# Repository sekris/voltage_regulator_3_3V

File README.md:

# voltage_regulator_3_3V
5v to 3.3v voltage regulator

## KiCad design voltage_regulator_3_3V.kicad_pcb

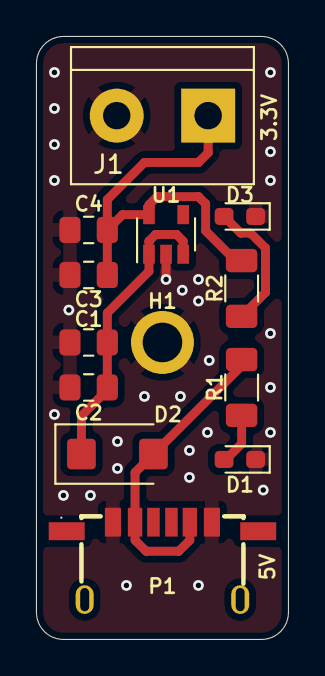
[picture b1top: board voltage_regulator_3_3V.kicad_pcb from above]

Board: 2 copper layers, 14.0 x 33.5 mm, 13 parts (0 on the bottom side), 6 nets.

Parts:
C1, C3: 10uF; C_0805_2012Metric_Pad1.18x1.45mm_HandSolder
C2, C4: 100nF; C_0805_2012Metric_Pad1.18x1.45mm_HandSolder
D1, D3: LED; LED_0603_1608Metric_Pad1.05x0.95mm_HandSolder
D2: SK16-DIO; P25_DO-214AC_SMA
H1: MountingHole_Pad; MountingHole_2.2mm_M2_ISO7380_Pad
J1: Screw_Terminal_01x02; TerminalBlock_bornier-2_P5.08mm
P1: USB_C_Plug_USB2.0; USB-C-SMD_USB-TYPE-C-006_USB-TYPE-C-006_C2927026
R1, R2: 330; R_1206_3216Metric_Pad1.30x1.75mm_HandSolder
U1: AP2112K-3.3; SOT-23-5

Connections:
/3.3V: C3.1, C4.1, J1.1, R2.1, U1.5 (VOUT)
/5V: D2.2 (A), P1.A9 (VBUS), P1.B9 (VBUS), R1.1
GND: C1.2, C2.2, C3.2, C4.2, D1.1 (K), D3.1 (K), H1.1 (1_1), J1.2, P1.A12 (GND), P1.B12 (GND), U1.2 (GND)
unnamed: D1.2 (A), R1.2
unnamed: C1.1, C2.1, D2.1 (K), U1.1 (VIN), U1.3 (EN)
unnamed: D3.2 (A), R2.2
